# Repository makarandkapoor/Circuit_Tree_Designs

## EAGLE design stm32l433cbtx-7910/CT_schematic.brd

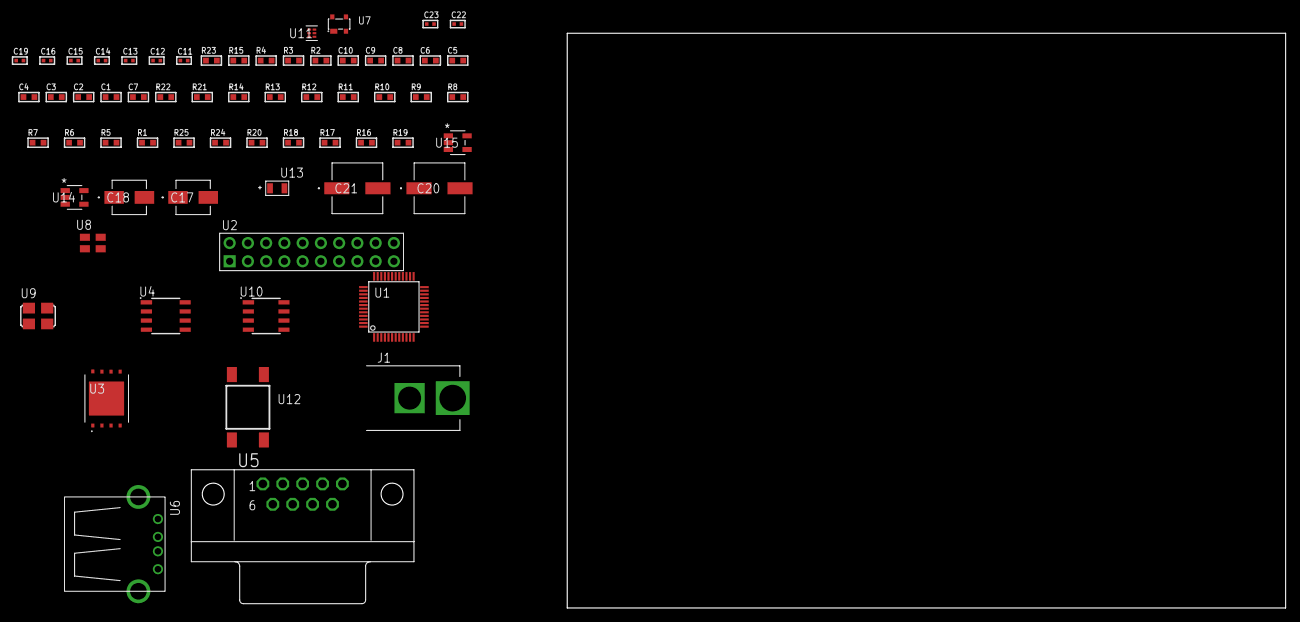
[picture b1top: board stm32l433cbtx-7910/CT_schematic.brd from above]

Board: 2 copper layers, 100.0 x 80.0 mm, 64 parts (0 on the bottom side), 37 nets, no tracks yet.

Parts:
C1, C9: 1e-06; C0603
C2, C3, C4, C5, C6, C10: 1e-07; C0603
C7: 4.7e-06; C0603
C8: 1e-08; C0603
C11, C12, C14, C19: 1e-07; C0402
C13, C15, C16, C22, C23: 1e-08; C0402
C17: 1e-06; EXV-9B
C18: 2.2e-06; EXV-9B
C20, C21: 0.0001; EXV-9H
J1: PJ-037B; PJ-037B_PACKAGE
R1, R5, R6, R7, R8, R9, R10, R11, R12, R13, R14, R21, R22: 10000.0; R0603
R2: 1000.0; R0603
R3: 1600.5; R0603
R4: 4700.0; R0603
R15: 120.0; R0603
R16: 470000.0; R0603
R17, R18, R20: 100000.0; R0603
R19: 164658.62; R0603
R23: 9100.0; R0603
R24: 680000.0; R0603
R25: 120000.0; R0603
U1: STM32L433CBT6; LQFP48
U2: TST-110-05-T-D-RA
U3: S25FL128SDPNFI001; WNG008
U4: SN65HVD230D; SOIC-8
U5: 182-009-113R531; 182-009-MALE
U6: 61400416021; USB-A-H
U7: prtr5v0u2ax; SOT143B
U8: ASEK-32.768KHz-ECST; ASEK
U9: ASFL1-25MHZ-NCS; ASFL1
U10: LP2954AIMX/NOPB; LP2954
U11: TPS3895ADRYR; SON-6
U12: 4-1437565-2; SW_4-1437565-2
U13: Q65110A2395; LGM67K-G1J2-24-Z
U14, U15: nc7sz125m5x; NC7SZ125M5X

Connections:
CLK_U1_3: U1.3, U8.3
CLK_U1_5: U1.5, U9.3
GND: C1.2, C2.2, C3.2, C4.2, C5.2, C6.2, C7.2, C8.2, C9.2, C10.2, C11.2, C12.2, C13.2, C14.2, C15.2, C16.2, C17.2, C18.2, C19.2, C20.2, C21.2, C22.2, C23.2, J1.2, R2.2, R5.2, R11.2, R16.2, R20.2, R23.2, R25.2, U1.8, U1.23, U1.35, U1.47, U2.4, U2.6, U2.8, U2.10, U2.12, U2.14, U2.16, U2.18, U2.20, U3.4, U3.PAD, U4.2, U5.5, U6.4, U6.5, U6.6, U7.1, U8.2, U9.2, U10.4, U11.2, U13.C, U14.2, U14.3, U15.1, U15.3
NET_U1_7: R4.1, U1.7, U15.4
NET_U1_43: R3.1, U1.43, U13.A
NET_U1_44: R1.1, R5.1, U1.44, U12.3, U12.4
NET_U2_19: R11.1, U2.19
NET_U3_3: R12.1, U3.3
NET_U3_7: R14.1, U3.7
NET_U4_6: R15.2, U4.6
NET_U4_8: R16.1, U4.8
NET_U5_2: R15.2, U4.6, U5.2
NET_U5_3: R15.1, U4.7, U5.3
NET_U7_4: U6.1, U7.4
NET_U10_3: R18.1, U10.3
NET_U10_5: R17.1, U10.5
NET_U10_7: R19.2, R20.1, U10.7
NET_U11_1: R22.1, R23.1, U11.1
NET_U11_3: R24.2, R25.1, U11.3
NET_U11_4: R21.1, U11.4, U14.4, U15.2
NET_U12_1: R2.1, U12.1, U12.2
PROC_CAN1_RX: U1.45, U4.4
PROC_CAN1_TX: U1.46, U4.1
PROC_SPI1_MISO: U1.16, U3.2
PROC_SPI1_MOSI: U1.17, U3.5
PROC_SPI1_NSS: R13.1, U1.14, U3.1
PROC_SPI1_SCK: U1.11, U3.6
PROC_SYS_JTCK_SWCLK: R9.1, U1.37, U2.9
PROC_SYS_JTDI: R7.1, U1.38, U2.5
PROC_SYS_JTDO_SWO: U1.39, U2.13
PROC_SYS_JTMS_SWDIO: R8.1, U1.34, U2.7
PROC_SYS_JTRST: R6.1, U1.40, U2.3
PROC_USB_DM: U1.32, U6.2, U7.3
PROC_USB_DP: U1.33, U6.3, U7.2
RST_OUT_U2_SRESET_B: R10.1, U2.15, U14.1
VCC_S1_9V7: C17.1, C20.1, C21.1, J1.1, R18.2, U10.8
VCC_TIER1_3V3: C1.1, C2.1, C3.1, C4.1, C5.1, C6.1, C7.1, C8.1, C9.1, C10.1, C11.1, C12.1, C13.1, C14.1, C15.1, C16.1, C18.1, C19.1, C22.1, C23.1, R1.2, R3.2, R4.2, R6.2, R7.2, R8.2, R9.2, R10.2, R12.2, R13.2, R14.2, R17.2, R19.1, R21.2, R22.2, R24.1, U1.1, U1.9, U1.24, U1.36, U1.48, U2.1, U2.2, U3.8, U4.3, U8.4, U9.4, U10.1, U11.6, U14.5, U15.5

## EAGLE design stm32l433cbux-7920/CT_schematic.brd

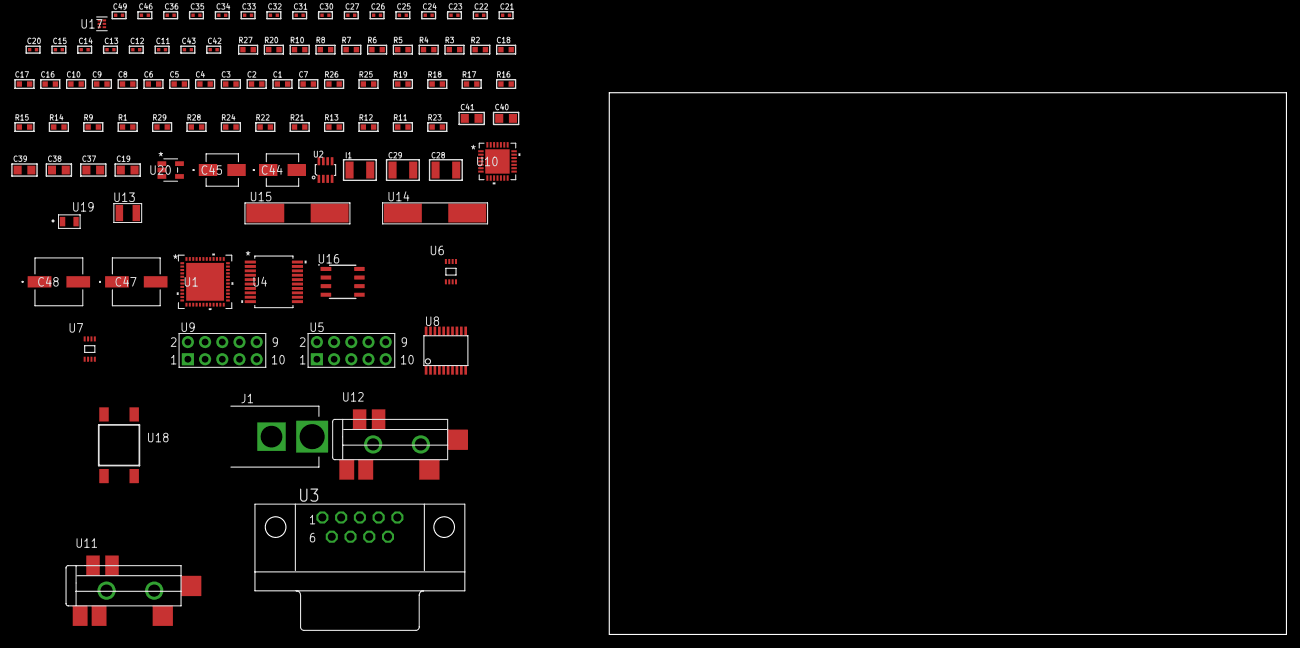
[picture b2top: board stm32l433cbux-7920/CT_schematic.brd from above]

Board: 2 copper layers, 100.0 x 80.0 mm, 100 parts (0 on the bottom side), 69 nets, no tracks yet.

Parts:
C1, C9, C16, C17, C18: 1e-06; C0603
C2, C3, C4, C5, C6, C10: 1e-07; C0603
C7: 4.7e-06; C0603
C8: 1e-08; C0603
C11, C12, C13, C14: 1e-11; C0402
C15, C22, C23, C24, C25, C26, C27, C32, C33, C34, C35, C36, C46: 1e-07; C0402
C19: 4.7e-06; C0805
C20, C21, C49: 1e-08; C0402
C28, C29: 2.2e-05; C1210
C30, C31: 1e-09; C0402
C37, C38, C39, C40, C41: 1e-05; C0805
C42, C43: 2.2e-11; C0402
C44: 1e-06; EXV-9B
C45: 2.2e-06; EXV-9B
C47, C48: 0.0001; EXV-9H
I1: 1.5e-05; L1210
J1: PJ-037B; PJ-037B_PACKAGE
R1, R9, R14, R15, R16, R25, R26: 10000.0; R0603
R2: 1000.0; R0603
R3: 1600.5; R0603
R4: 4700.0; R0603
R5, R6, R7, R8: 2200.0; R0603
R10: 120.0; R0603
R11, R12, R13, R21, R22, R24: 100000.0; R0603
R17, R18, R19: 47000.0; R0603
R20: 680.0; R0603
R23: 164658.62; R0603
R27: 9100.0; R0603
R28: 680000.0; R0603
R29: 120000.0; R0603
U1: STM32L433CBU6; UFQFPN48
U2: MAX3051EKA+T; SOT-23-8
U3: 182-009-113R531; 182-009-MALE
U4: MAX3218EAP+T; SSOP-20
U5, U9: HTSS-105-01-G-D
U6: 24AA00T-I/MNY; TDFN-8/6MM
U7: 24AA128T-I/MNY; TDFN-8/6MM
U8: SP3203ECY-L/TR; TSSOP20-I
U10: WM8731CLSEFL; QFN-28
U11, U12: SJ-43515TS-SMT-TR
U13: ABS07-32.768KHZ-7-T
U14: ABLS-25.000MHZ-B2F-T
U15: ABLS-12.288MHZ-B4-T
U16: LP2954AIMX/NOPB; LP2954
U17: TPS3895ADRYR; SON-6
U18: 4-1437565-2; SW_4-1437565-2
U19: Q65110A2395; LGM67K-G1J2-24-Z
U20: nc7sz125m5x; NC7SZ125M5X

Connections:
CLK_CRYSTAL_U1_3: C11.1, U1.3, U13.1
CLK_CRYSTAL_U1_4: C12.1, U1.4, U13.2
CLK_CRYSTAL_U1_5: C13.1, U1.5, U14.1
CLK_CRYSTAL_U1_6: C14.1, U1.6, U14.2
CLK_CRYSTAL_U10_1: C42.1, U10.1, U15.1
CLK_CRYSTAL_U10_2: C43.1, U10.2, U15.2
GND: C1.2, C2.2, C3.2, C4.2, C5.2, C6.2, C7.2, C8.2, C9.2, C10.2, C11.2, C12.2, C13.2, C14.2, C15.2, C16.2, C17.2, C18.2, C20.2, C21.2, C22.2, C23.2, C26.2, C27.2, C31.2, C32.2, C33.2, C34.2, C35.2, C36.2, C37.2, C38.2, C39.2, C40.2, C41.2, C42.2, C43.2, C44.2, C45.2, C46.2, C47.2, C48.2, C49.2, J1.2, R2.2, R9.2, R14.2, R16.2, R17.2, R18.2, R19.2, R24.2, R27.2, R29.2, U1.8, U1.23, U1.35, U1.47, U1.49, U2.2, U2.8, U3.5, U4.5, U4.17, U4.20, U5.9, U6.4, U7.4, U8.18, U9.9, U10.4, U10.15, U10.19, U10.25, U10.26, U10.29, U11.1, U12.1, U16.4, U17.2, U19.C, U20.1, U20.3
NET_U1_7: R4.1, U1.7, U20.4
NET_U1_21: R7.1, U1.21, U7.6
NET_U1_22: R8.1, U1.22, U7.5
NET_U1_31: R6.1, U1.31, U6.5
NET_U1_42: R5.1, U1.42, U6.6
NET_U1_44: R9.1, U1.44
NET_U1_45: R3.1, U1.45, U19.A
NET_U1_46: R1.1, U1.46, U18.3, U18.4
NET_U2_6: R10.2, U2.6
NET_U3_2: R10.2, U2.6, U3.2
NET_U3_3: R10.1, U2.7, U3.3
NET_U4_1: I1.1, U4.1
NET_U4_2: R11.1, U4.2
NET_U4_3: R12.1, U4.3
NET_U4_4: R13.1, U4.4
NET_U4_15: C18.1, U4.15
NET_U4_16: C19.2, U4.16
NET_U4_18: C19.1, U4.18
NET_U4_19: C17.1, U4.19
NET_U5_3: U4.12, U5.3
NET_U5_4: U4.11, U5.4
NET_U5_5: U4.14, U5.5
NET_U5_6: U4.13, U5.6
NET_U7_1: R14.1, U7.1
NET_U7_2: R15.1, U7.2
NET_U7_3: R16.1, U7.3
NET_U8_1: C24.1, U8.1
NET_U8_2: C26.1, U8.2
NET_U8_3: C24.2, U8.3
NET_U8_4: C25.1, U8.4
NET_U8_5: C25.2, U8.5
NET_U8_6: C27.1, U8.6
NET_U9_3: U8.14, U9.3
NET_U9_4: U8.13, U9.4
NET_U9_5: U8.17, U9.5
NET_U9_6: U8.16, U9.6
NET_U10_20: C36.1, C41.1, U10.20
NET_U11_2: C29.1, R18.1, U11.2
NET_U11_5: C28.1, R17.1, U11.5
NET_U12_5: C30.1, C31.1, R19.1, R20.1, U12.5
NET_U16_3: R22.1, U16.3
NET_U16_5: R21.1, U16.5
NET_U16_7: R23.2, R24.1, U16.7
NET_U17_1: R26.1, R27.1, U17.1
NET_U17_3: R28.2, R29.1, U17.3
NET_U17_4: R25.1, U17.4, U20.2
NET_U18_1: R2.1, U18.1, U18.2
PROC_CAN1_RX: U1.32, U2.4
PROC_CAN1_TX: U1.33, U2.1
PROC_LPUART1_CTS: U1.16, U4.8
PROC_LPUART1_RTS: U1.19, U4.10
PROC_LPUART1_RX: U1.13, U4.9
PROC_LPUART1_TX: U1.12, U4.7
PROC_SAI1_FS_A: U1.25, U10.9, U10.11
PROC_SAI1_SCK_A: U1.26, U10.7
PROC_SAI1_SD_A: U1.28, U10.8
PROC_USART1_CTS: U1.40, U8.8
PROC_USART1_RTS: U1.39, U8.10
PROC_USART1_RX: U1.43, U8.11
PROC_USART1_TX: U1.30, U8.7
VCC_S1_5V3: C44.1, C47.1, C48.1, J1.1, R22.2, U16.8
VCC_TIER1_3V3: C1.1, C2.1, C3.1, C4.1, C5.1, C6.1, C7.1, C8.1, C9.1, C10.1, C15.1, C16.1, C20.1, C21.1, C22.1, C23.1, C32.1, C33.1, C34.1, C35.1, C37.1, C38.1, C39.1, C40.1, C45.1, C46.1, C49.1, I1.2, R1.2, R3.2, R4.2, R5.2, R6.2, R7.2, R8.2, R11.2, R12.2, R13.2, R15.2, R21.2, R23.1, R25.2, R26.2, R28.1, U1.1, U1.9, U1.24, U1.36, U1.48, U2.3, U4.6, U6.8, U7.7, U7.8, U8.12, U8.19, U10.3, U10.5, U10.12, U10.18, U16.1, U17.6, U20.5

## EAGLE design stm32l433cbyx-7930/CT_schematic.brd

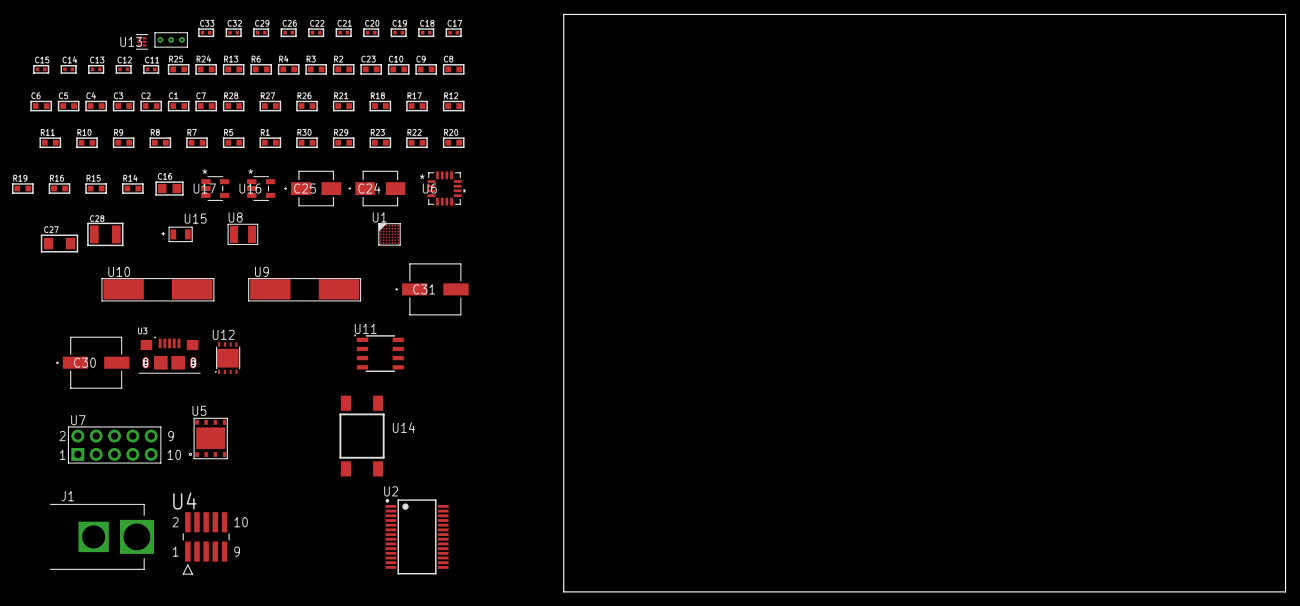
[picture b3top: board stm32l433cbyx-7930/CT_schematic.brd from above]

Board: 2 copper layers, 82 parts (0 on the bottom side), 57 nets, no tracks yet.

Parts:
C1, C9, C23: 1e-06; C0603
C2, C3, C4, C5, C6, C10: 1e-07; C0603
C7: 4.7e-06; C0603
C8: 1e-08; C0603
C11, C12, C13, C14: 1e-11; C0402
C15, C17, C18, C19, C20, C21, C22, C29: 1e-07; C0402
C16: 4.7e-06; C0805
C24: 1e-06; EXV-9B
C25: 2.2e-06; EXV-9B
C26, C32, C33: 1e-08; C0402
C27: 1e-05; C1206
C28: 1e-05; C1210
C30, C31: 0.0001; EXV-9H
J1: PJ-037B; PJ-037B_PACKAGE
R1, R5, R7, R8, R9, R10, R11, R12, R17, R18, R26, R27: 10000.0; R0603
R2, R25: 1000.0; R0603
R3: 910.0; R0603
R4, R6: 4700.0; R0603
R13: 5.0; R0603
R14, R15, R16, R19, R20, R22, R23: 100000.0; R0603
R21: 47000.0; R0603
R24: 2231.0; R0603
R28: 82000.0; R0603
R29: 300000.0; R0603
R30: 120000.0; R0603
U1: STM32L433CBY6; WLCSP49
U2: FT232RL-REEL; SSOP-28
U3: 10118193-0001LF; FCI_10118193-0001LF
U4: FTSH-105-01-L-DV-K; SAMTEC_FTSH-105-01-L-DV-K
U5: SST26WF016B-104I/MF; WFDN-8
U6: TSC2046IRGVR; VQFN-16
U7: HTSS-105-01-G-D
U8: ABS07-32.768KHZ-7-T
U9: ABLS-25.000MHZ-B2F-T
U10: ABLS-12.000MHZ-B4-T
U11: LP2954AIMX/NOPB; LP2954
U12: LP3878SDX-ADJ/NOPB; WSON-8
U13: TPS3895ADRYR; SON-6
U14: 4-1437565-2; SW_4-1437565-2
U15: Q65110A2395; LGM67K-G1J2-24-Z
U16, U17: nc7sz125m5x; NC7SZ125M5X
U18: Dummy; DUMMY_PACKAGE_172

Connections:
CLK_CRYSTAL_U1_C6: C11.1, U1.C6, U8.1
CLK_CRYSTAL_U1_C7: C12.1, U1.C7, U8.2
CLK_CRYSTAL_U1_D6: C13.1, U1.D6, U9.1
CLK_CRYSTAL_U1_D7: C14.1, U1.D7, U9.2
CLK_CRYSTAL_U2_27: U2.27, U10.1
CLK_CRYSTAL_U2_28: U2.28, U10.2
GND: C1.2, C2.2, C3.2, C4.2, C5.2, C6.2, C7.2, C8.2, C9.2, C10.2, C11.2, C12.2, C13.2, C14.2, C15.2, C16.2, C17.2, C18.2, C19.2, C20.2, C21.2, C22.2, C23.2, C24.2, C25.2, C26.2, C27.2, C28.2, C29.2, C30.2, C31.2, C32.2, C33.2, J1.2, R2.2, R5.2, R8.2, R12.2, R13.2, R22.2, R25.2, R28.2, R30.2, U1.A6, U1.B1, U1.E7, U1.G2, U2.7, U2.18, U2.21, U2.25, U2.26, U3.5, U3.6, U3.7, U3.8, U3.9, U4.3, U4.5, U5.4, U5.9, U6.10, U7.9, U11.4, U12.3, U12.PAD, U13.2, U15.C, U16.2, U16.3, U17.1, U17.3, U18.1
NET_U1_A5: R5.1, U1.A5
NET_U1_D5: R4.1, U1.D5, U17.4
NET_U1_G3: R3.1, U1.G3, U15.A
NET_U1_G7: R1.1, U1.G7, U14.3, U14.4
NET_U2_14: R7.1, U2.14
NET_U2_17: C17.1, U2.17
NET_U2_19: R8.1, U2.19
NET_U3_1: R6.1, U3.1
NET_U3_2: U2.16, U3.2
NET_U3_3: U2.15, U3.3
NET_U4_9: R13.1, U4.9
NET_U6_15: R18.1, U6.15
NET_U7_3: U6.7, U7.3
NET_U7_4: U6.9, U7.4
NET_U7_5: U6.6, U7.5
NET_U7_6: U6.8, U7.6
NET_U11_3: R20.1, U11.3
NET_U11_5: R19.1, U11.5
NET_U11_7: R21.2, R22.1, U11.7
NET_U12_1: C26.1, U12.1
NET_U12_6: R24.2, R25.1, U12.6
NET_U12_8: R23.1, U12.8
NET_U13_1: R27.1, R28.1, U13.1
NET_U13_3: R29.2, R30.1, U13.3
NET_U13_4: R26.1, U13.4, U16.4, U17.2
NET_U14_1: R2.1, U14.1, U14.2
PROC_LPUART1_CTS: U1.E2, U2.3
PROC_LPUART1_RTS: U1.F1, U2.11
PROC_LPUART1_RX: U1.E4, U2.1
PROC_LPUART1_TX: U1.F2, U2.5
PROC_QUADSPI_BK1_IO0: U1.G4, U5.5
PROC_QUADSPI_BK1_IO1: U1.G5, U5.2
PROC_QUADSPI_BK1_IO2: R15.1, U1.F3, U5.3
PROC_QUADSPI_BK1_IO3: R16.1, U1.F4, U5.7
PROC_QUADSPI_BK1_NCS: R14.1, U1.E5, U5.1
PROC_QUADSPI_CLK: U1.E3, U5.6
PROC_SPI1_MISO: U1.A4, U6.16
PROC_SPI1_MOSI: U1.B4, U6.2
PROC_SPI1_NSS: R17.1, U1.G6, U6.3
PROC_SPI1_SCK: U1.F5, U6.4
PROC_SYS_JTCK_SWCLK: R12.1, U1.A2, U4.4
PROC_SYS_JTDI: R10.1, U1.B3, U4.8
PROC_SYS_JTDO_SWO: U1.A3, U4.6
PROC_SYS_JTMS_SWDIO: R11.1, U1.B2, U4.2
PROC_TIM1_CH2: U1.D2, U18.2
PROC_TIM1_CH4: U1.C1, U18.3
RST_OUT_U4_JTAG_RST_B: R9.1, U4.10, U16.1
VCC_S1_8V5: C24.1, C27.1, C30.1, C31.1, J1.1, R20.2, R23.2, U11.8, U12.4
VCC_TIER1_1V8: C1.1, C2.1, C3.1, C4.1, C5.1, C6.1, C7.1, C8.1, C9.1, C10.1, C18.1, C19.1, C20.1, C21.1, C25.1, C29.1, C32.1, C33.1, R1.2, R3.2, R4.2, R9.2, R10.2, R11.2, R14.2, R15.2, R16.2, R17.2, R18.2, R19.2, R21.1, R26.2, R27.2, R29.1, U1.A1, U1.A7, U1.B6, U1.F7, U1.G1, U2.4, U4.1, U5.8, U6.14, U11.1, U13.6, U16.5, U17.5
VCC_TIER1_3V3: C15.1, C16.1, C22.1, C23.1, C28.1, R7.2, R24.1, U2.20, U6.5, U12.5

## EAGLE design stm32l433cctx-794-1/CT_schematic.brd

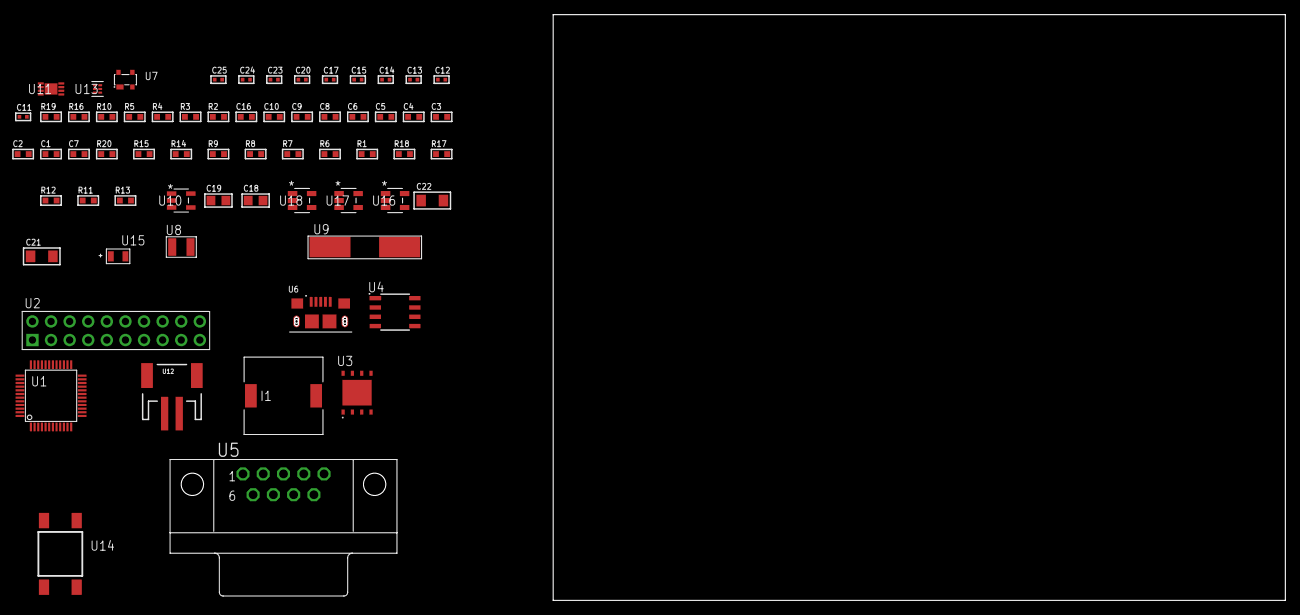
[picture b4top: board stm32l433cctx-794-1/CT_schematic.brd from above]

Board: 2 copper layers, 64 parts (0 on the bottom side), 38 nets, no tracks yet.

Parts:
C1, C9, C16: 1e-06; C0603
C2, C3, C4, C5, C6, C10: 1e-07; C0603
C7: 4.7e-06; C0603
C8: 1e-08; C0603
C11, C12, C13, C14: 1e-11; C0402
C15, C17, C20: 1e-07; C0402
C18, C19: 1e-05; C0805
C21, C22: 1e-05; C1206
C23, C24, C25: 1e-08; C0402
I1: 5.2e-06; DR1040
R1, R6, R7, R8, R9, R14, R15, R20: 10000.0; R0603
R2: 1000.0; R0603
R3: 1600.5; R0603
R4, R5: 4700.0; R0603
R10: 120.0; R0603
R11: 100000.0; R0603
R12: 220000.0; R0603
R13: 1000000.0; R0603
R16: 9100.0; R0603
R17: 680000.0; R0603
R18: 120000.0; R0603
R19: 2000.0; R0603
U1: STM32L433CCT6; LQFP48
U2: TST-110-05-T-D-RA
U3: MX25R6435FZAIH0; WSON-8-PAD
U4: SN65HVD230D; SOIC-8
U5: 182-009-113R531; 182-009-MALE
U6: 10118193-0001LF; FCI_10118193-0001LF
U7: prtr5v0u2ax; SOT143B
U8: ABS07-32.768KHZ-7-T
U9: ABLS-25.000MHZ-B2F-T
U10: ltc3406es5; TSOT-23-5
U11: MCP73831T-2ACI/MC; DFN8_2X3MC
U12: S2B-PH-SM4-TB(LF)(SN); JST-2-SMD
U13: TPS3895ADRYR; SON-6
U14: 4-1437565-2; SW_4-1437565-2
U15: Q65110A2395; LGM67K-G1J2-24-Z
U16, U17, U18: nc7sz125m5x; NC7SZ125M5X

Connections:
CLK_CRYSTAL_U1_3: C11.1, U1.3, U8.1
CLK_CRYSTAL_U1_4: C12.1, U1.4, U8.2
CLK_CRYSTAL_U1_5: C13.1, U1.5, U9.1
CLK_CRYSTAL_U1_6: C14.1, U1.6, U9.2
GND: C1.2, C2.2, C3.2, C4.2, C5.2, C6.2, C7.2, C8.2, C9.2, C10.2, C11.2, C12.2, C13.2, C14.2, C15.2, C16.2, C17.2, C18.2, C19.1, C19.2, C20.2, C21.2, C22.2, C23.2, C24.2, C25.2, R2.2, R6.2, R11.2, R12.2, R16.2, R18.2, R19.2, U1.8, U1.23, U1.35, U1.47, U2.4, U2.6, U2.8, U2.10, U2.12, U2.14, U2.16, U2.18, U2.20, U3.4, U3.PAD, U4.2, U5.5, U6.5, U6.6, U6.7, U6.8, U6.9, U7.1, U10.2, U11.6, U11.9, U12.2, U13.2, U15.C, U16.2, U16.3, U17.1, U17.3, U18.1, U18.3
INPUT_USBPOWER_5V: C21.1, R20.2, U6.1, U7.4, U11.1, U11.2
NET_U1_7: R5.1, U1.7, U18.4
NET_U1_43: R3.1, U1.43, U15.A
NET_U1_44: R1.1, R6.1, U1.44, U14.3, U14.4
NET_U3_7: R4.1, U1.16, U3.7, U17.4
NET_U4_6: R10.2, U4.6
NET_U4_8: R11.1, U4.8
NET_U5_2: R10.2, U4.6, U5.2
NET_U5_3: R10.1, U4.7, U5.3
NET_U10_3: I1.1, U10.3
NET_U10_5: R12.1, R13.1, U10.5
NET_U10_ATNET_3: I1.2, R13.2
NET_U11_5: R20.1, U11.5
NET_U11_8: R19.1, U11.8
NET_U13_1: R15.1, R16.1, U13.1
NET_U13_3: R17.2, R18.1, U13.3
NET_U13_4: R14.1, U13.4, U16.4, U17.2, U18.2
NET_U14_1: R2.1, U14.1, U14.2
PROC_CAN1_RX: U1.45, U4.4
PROC_CAN1_TX: U1.46, U4.1
PROC_QUADSPI_BK1_IO0: U1.19, U3.5
PROC_QUADSPI_BK1_IO1: U1.18, U3.2
PROC_QUADSPI_BK1_IO2: R9.1, U1.17, U3.3
PROC_QUADSPI_BK1_NCS: R8.1, U1.12, U3.1
PROC_QUADSPI_CLK: U1.13, U3.6
PROC_SYS_JTCK_SWCLK: U1.37, U2.9
PROC_SYS_JTDO_SWO: U1.39, U2.13
PROC_SYS_JTMS_SWDIO: U1.34, U2.7
PROC_USB_DM: U1.32, U6.2, U7.3
PROC_USB_DP: U1.33, U6.3, U7.2
RST_OUT_U2_SRESET_B: R7.1, U2.15, U16.1
VCC_S1_3V7: C18.1, C22.1, U10.4, U11.3, U11.4, U12.1
VCC_TIER1_3V3: C1.1, C2.1, C3.1, C4.1, C5.1, C6.1, C7.1, C8.1, C9.1, C10.1, C15.1, C16.1, C17.1, C19.2, C20.1, C23.1, C24.1, C25.1, I1.2, R1.2, R3.2, R4.2, R5.2, R7.2, R8.2, R9.2, R13.2, R14.2, R15.2, R17.1, U1.1, U1.9, U1.24, U1.36, U1.48, U2.1, U3.8, U4.3, U13.6, U16.5, U17.5, U18.5

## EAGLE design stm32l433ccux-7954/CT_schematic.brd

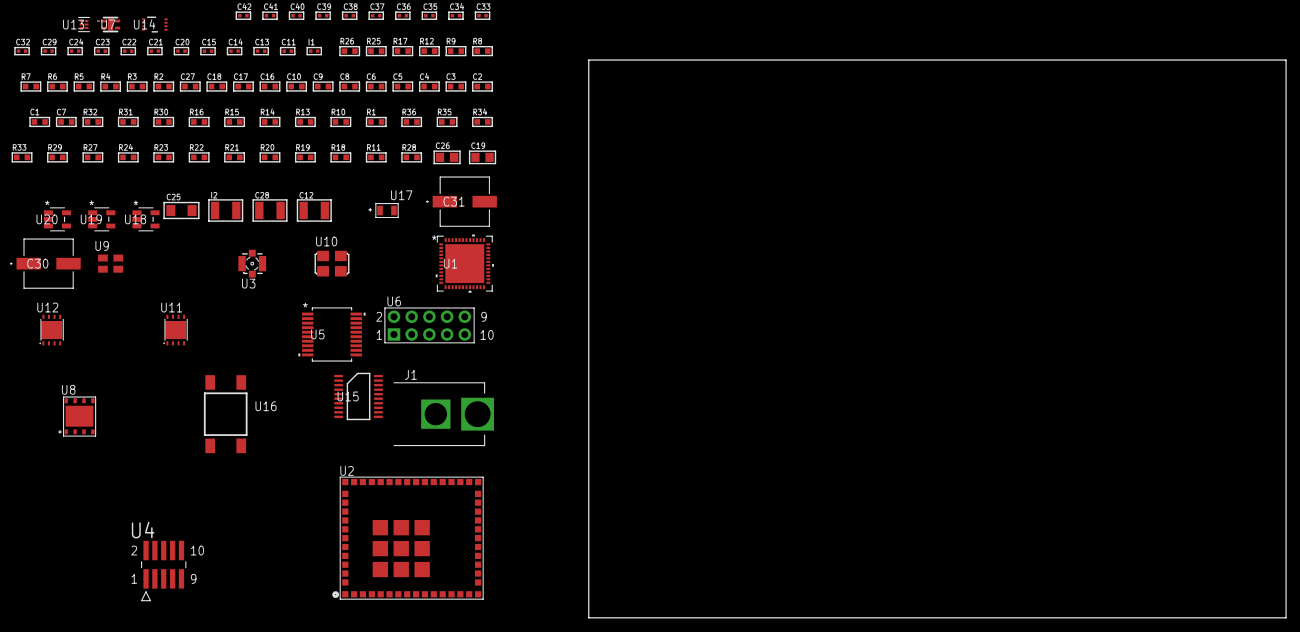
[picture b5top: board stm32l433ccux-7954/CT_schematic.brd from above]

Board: 2 copper layers, 100.0 x 80.0 mm, 101 parts (0 on the bottom side), 65 nets, no tracks yet.

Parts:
C1, C9, C16, C17, C18, C27: 1e-06; C0603
C2, C3, C4, C5, C6, C10: 1e-07; C0603
C7: 4.7e-06; C0603
C8: 1e-08; C0603
C11: 1e-12; C0402
C12: 2.2e-05; C1210
C13, C14, C15, C20, C21, C29, C33, C35, C37, C39: 1e-07; C0402
C19: 4.7e-06; C0805
C22, C23, C24, C32, C34, C36, C38, C40, C41, C42: 1e-08; C0402
C25: 1e-05; C1206
C26: 1e-05; C0805
C28: 1e-05; C1210
C30, C31: 0.0001; EXV-9H
I1: 3.6e-09; C0402
I2: 1.5e-05; L1210
J1: PJ-037B; PJ-037B_PACKAGE
R1, R10, R13, R14, R15, R16, R30, R31: 10000.0; R0603
R2, R26: 1000.0; R0603
R3: 910.0; R0603
R4, R5: 4700.0; R0603
R6, R7, R8, R9: 2200.0; R0603
R11, R18, R19, R20, R21, R22, R23, R24, R27, R29: 100000.0; R0603
R12: 2700.0; R0603
R17: 5.0; R0603
R25: 806.0; R0603
R28: 153694.38; R0603
R32: 82000.0; R0603
R33: 300000.0; R0603
R34: 120000.0; R0603
R35, R36: 200000.0; R0603
U1: STM32L433CCU6; UFQFPN48
U2: CC3200MODR1M2AMOBT; LGA63S127P16X13_2050X1750X150
U3: 73412-0114; COAXIAL_C
U4: FTSH-105-01-L-DV-K; SAMTEC_FTSH-105-01-L-DV-K
U5: MAX3218EAP+T; SSOP-20
U6: HTSS-105-01-G-D
U7: Si7034-A10-IM; SI7034-A10-IM
U8: SST26VF032B-104I/MF; WFDN-8
U9: ASEK-32.768KHz-ECST; ASEK
U10: ASFL1-25MHZ-NCS; ASFL1
U11: LP3878SDX-ADJ/NOPB; WSON-8
U12: LP2951ACSDX/NOPB; WSON-8
U13: TPS3895ADRYR; SON-6
U14: LSF0102DCTR; DCU0008A_N
U15: LSF0108PWR; PW0020A
U16: 4-1437565-2; SW_4-1437565-2
U17: Q65110A2395; LGM67K-G1J2-24-Z
U18, U19, U20: nc7sz125m5x; NC7SZ125M5X

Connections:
CLK_U1_3: U1.3, U9.3
CLK_U1_5: U1.5, U10.3
GND: C1.2, C2.2, C3.2, C4.2, C5.2, C6.2, C7.2, C8.2, C9.2, C10.2, C11.2, C12.2, C13.2, C14.2, C15.2, C16.2, C17.2, C18.2, C20.2, C21.2, C22.2, C23.2, C24.2, C25.2, C26.2, C27.2, C28.2, C29.2, C30.2, C31.2, C32.2, C33.2, C34.2, C35.2, C36.2, C37.2, C38.2, C39.2, C40.2, C41.2, C42.2, J1.2, R2.2, R10.2, R11.2, R12.2, R16.2, R17.2, R26.2, R29.2, R32.2, R34.2, U1.8, U1.23, U1.35, U1.47, U1.49, U2.1, U2.2, U2.16, U2.27, U2.28, U2.30, U2.32, U2.38, U2.43, U2.55, U2.56, U2.57, U2.58, U2.59, U2.60, U2.61, U2.62, U2.63, U3.1, U3.2, U3.3, U3.4, U4.3, U4.5, U5.5, U5.17, U5.20, U6.9, U7.5, U8.4, U8.9, U9.2, U10.2, U11.3, U11.PAD, U12.3, U12.4, U12.PAD, U13.2, U14.1, U15.1, U17.C, U18.2, U18.3, U19.1, U19.3, U20.1, U20.3
NET_U1_7: R5.1, U1.7, U20.4
NET_U1_21: R8.1, U1.21, U7.2
NET_U1_22: R9.1, U1.22, U7.4
NET_U1_31: R7.1, U1.31, U14.3
NET_U1_42: R6.1, U1.42, U14.4
NET_U1_44: R10.1, U1.44
NET_U1_45: R3.1, U1.45, U17.A
NET_U1_46: R1.1, U1.46, U16.3, U16.4
NET_U2_21: R11.1, U2.21
NET_U2_23: R12.1, U2.23
NET_U2_35: R4.1, U2.35, U19.4
NET_U3_1: C11.1, I1.1, U3.1
NET_U4_9: R17.1, U4.9
NET_U5_1: I2.1, U5.1
NET_U5_2: R18.1, U5.2
NET_U5_3: R19.1, U5.3
NET_U5_4: R20.1, U5.4
NET_U5_15: C18.1, U5.15
NET_U5_16: C19.2, U5.16
NET_U5_18: C19.1, U5.18
NET_U5_19: C17.1, U5.19
NET_U6_3: U5.12, U6.3
NET_U6_4: U5.11, U6.4
NET_U6_5: U5.14, U6.5
NET_U6_6: U5.13, U6.6
NET_U11_1: C24.1, U11.1
NET_U11_6: R25.2, R26.1, U11.6
NET_U11_8: R24.1, U11.8
NET_U12_5: R27.1, U12.5
NET_U12_7: R28.2, R29.1, U12.7
NET_U13_1: R31.1, R32.1, U13.1
NET_U13_3: R33.2, R34.1, U13.3
NET_U13_4: R30.1, U13.4, U18.4, U19.2, U20.2
NET_U14_8: R35.1, U14.8
NET_U15_20: R36.1, U15.20
NET_U16_1: R2.1, U16.1, U16.2
PROC_I2C1_SCL_TOXCVR: U2.3, U14.5
PROC_I2C1_SDA_TOXCVR: U2.4, U14.6
PROC_QUADSPI_BK1_IO0_TOIOBUF: U1.19, U15.3
PROC_QUADSPI_BK1_IO0_TOXCVR: U8.5, U15.18
PROC_QUADSPI_BK1_IO1_TOIOBUF: U1.18, U15.7
PROC_QUADSPI_BK1_IO1_TOXCVR: U8.2, U15.14
PROC_QUADSPI_BK1_IO2_TOIOBUF: U1.17, U15.5
PROC_QUADSPI_BK1_IO2_TOXCVR: R22.1, U8.3, U15.16
PROC_QUADSPI_BK1_IO3_TOIOBUF: U1.16, U15.8
PROC_QUADSPI_BK1_IO3_TOXCVR: R23.1, U8.7, U15.13
PROC_QUADSPI_BK1_NCS_TOIOBUF: U1.12, U15.6
PROC_QUADSPI_BK1_NCS_TOXCVR: R21.1, U8.1, U15.15
PROC_QUADSPI_CLK_TOIOBUF: U1.13, U15.4
PROC_QUADSPI_CLK_TOXCVR: U8.6, U15.17
PROC_SYS_JTCK_SWCLK: R16.1, U1.37, U4.4
PROC_SYS_JTDI: R14.1, U1.38, U4.8
PROC_SYS_JTDO_SWO: U1.39, U4.6
PROC_SYS_JTMS_SWDIO: R15.1, U1.34, U4.2
PROC_USART1_CTS: U1.32, U5.8
PROC_USART1_RTS: U1.33, U5.10
PROC_USART1_RX: U1.43, U5.9
PROC_USART1_TX: U1.30, U5.7
RST_OUT_U4_JTAG_RST_B: R13.1, U4.10, U18.1
VCC_S1_7V4: C25.1, C27.1, C30.1, C31.1, J1.1, R24.2, U11.4, U12.8
VCC_TIER1_1V8: C1.1, C2.1, C3.1, C4.1, C5.1, C6.1, C7.1, C10.1, C15.1, C16.1, C20.1, C26.1, C29.1, C34.1, C35.1, C38.1, C39.1, C40.1, C41.1, C42.1, I2.2, R1.2, R3.2, R5.2, R6.2, R7.2, R8.2, R9.2, R13.2, R14.2, R15.2, R18.2, R19.2, R20.2, R25.1, R30.2, R31.2, R33.1, U1.1, U1.24, U1.36, U1.48, U4.1, U5.6, U7.1, U11.5, U13.6, U14.2, U15.2, U18.5, U19.5, U20.5
VCC_TIER1_3V3: C8.1, C9.1, C12.1, C13.1, C14.1, C21.1, C22.1, C23.1, C28.1, C32.1, C33.1, C36.1, C37.1, R4.2, R21.2, R22.2, R23.2, R27.2, R28.1, R35.2, R36.2, U1.9, U2.36, U2.37, U2.40, U8.8, U9.4, U10.4, U12.1, U14.7, U15.19

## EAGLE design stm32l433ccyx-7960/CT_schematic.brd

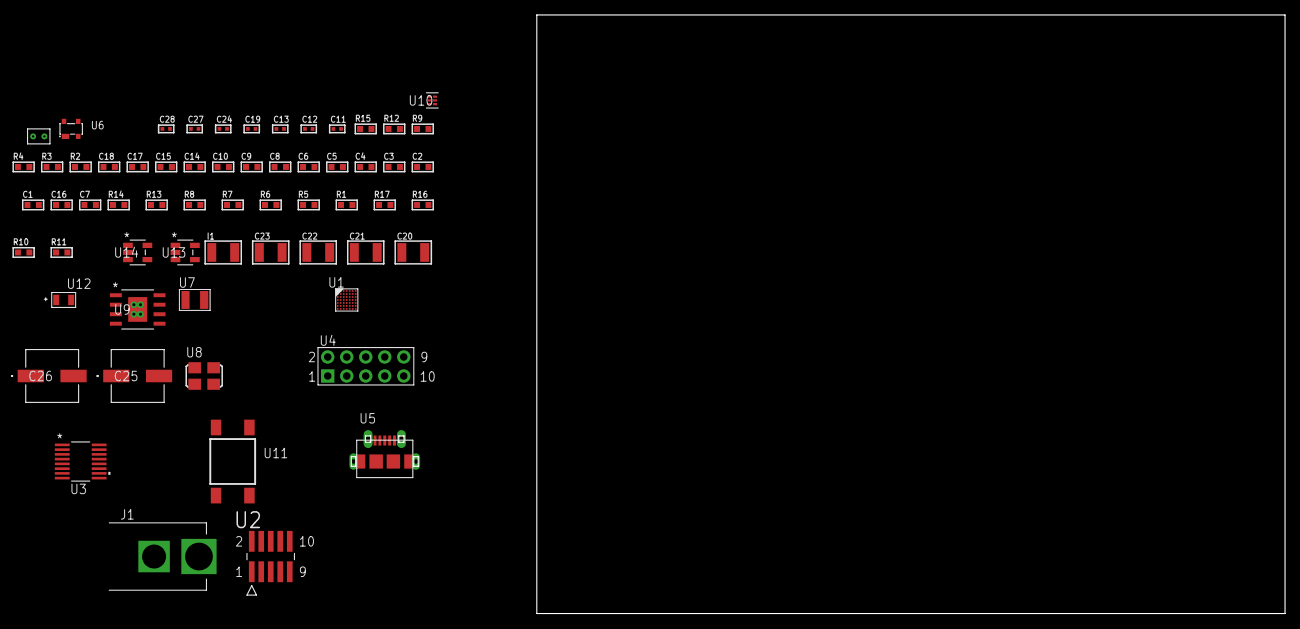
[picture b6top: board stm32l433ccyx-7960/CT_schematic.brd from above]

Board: 2 copper layers, 124.8 x 80.0 mm, 62 parts (0 on the bottom side), 37 nets, no tracks yet.

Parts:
C1, C9, C14, C15, C17, C18: 1e-06; C0603
C2, C3, C4, C5, C6, C10: 1e-07; C0603
C7: 4.7e-06; C0603
C8: 1e-08; C0603
C11, C12: 1e-11; C0402
C13, C24: 1e-07; C0402
C16: 2.2e-07; C0603
C19, C27, C28: 1e-08; C0402
C20, C21, C22, C23: 1e-05; C1210
C25, C26: 0.0001; EXV-9H
I1: 1e-05; L1210
J1: PJ-037B; PJ-037B_PACKAGE
R1, R5, R6, R7, R8, R13, R14: 10000.0; R0603
R2: 1000.0; R0603
R3: 1600.5; R0603
R4: 4700.0; R0603
R9: 5.0; R0603
R10: 100000.0; R0603
R11: 4031.5447154472; R0603
R12: 2200.0; R0603
R15: 9100.0; R0603
R16: 680000.0; R0603
R17: 120000.0; R0603
U1: STM32L433CCY6; WLCSP49
U2: FTSH-105-01-L-DV-K; SAMTEC_FTSH-105-01-L-DV-K
U3: LTC2804CGN-1#PBF; SSOP-16
U4: HTSS-105-01-G-D
U5: 47590-0001; MICRO_USB_AB
U6: prtr5v0u2ax; SOT143B
U7: ABS07-32.768KHZ-7-T
U8: ASFL1-25MHZ-NCS; ASFL1
U9: MIC5234YME; SOIC-8_EP
U10: TPS3895ADRYR; SON-6
U11: 4-1437565-2; SW_4-1437565-2
U12: Q65110A2395; LGM67K-G1J2-24-Z
U13, U14: nc7sz125m5x; NC7SZ125M5X
U15: Dummy; DUMMY_PACKAGE_127

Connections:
CLK_CRYSTAL_U1_C6: C11.1, U1.C6, U7.1
CLK_CRYSTAL_U1_C7: C12.1, U1.C7, U7.2
CLK_U1_D7: U1.D7, U8.3
GND: C1.2, C2.2, C3.2, C4.2, C5.2, C6.2, C7.2, C8.2, C9.2, C10.2, C11.2, C12.2, C13.2, C14.2, C15.2, C17.2, C18.2, C19.2, C20.2, C21.2, C22.2, C23.2, C24.2, C25.2, C26.2, C27.2, C28.2, J1.2, R2.2, R5.2, R9.2, R12.2, R15.2, R17.2, U1.A6, U1.B1, U1.E7, U1.G2, U2.3, U2.5, U3.8, U4.9, U5.5, U5.6, U5.7, U5.8, U5.9, U6.1, U8.2, U9.7, U9.EPAD, U10.2, U12.C, U13.2, U13.3, U14.1, U14.3, U15.1
NET_U1_A5: R5.1, U1.A5
NET_U1_D5: R4.1, U1.D5, U14.4
NET_U1_G6: R3.1, U1.G6, U12.A
NET_U1_G7: R1.1, U1.G7, U11.3, U11.4
NET_U2_9: R9.1, U2.9
NET_U3_6: C14.1, U3.6
NET_U3_7: C16.1, I1.2, U3.7
NET_U3_9: C15.1, U3.9
NET_U3_10: C16.2, U3.10
NET_U3_11: R10.1, U3.11
NET_U4_3: U3.1, U4.3
NET_U4_4: U3.2, U4.4
NET_U4_5: U3.3, U4.5
NET_U4_6: U3.4, U4.6
NET_U6_4: U5.1, U6.4
NET_U9_4: R11.2, R12.1, U9.4
NET_U10_1: R14.1, R15.1, U10.1
NET_U10_3: R16.2, R17.1, U10.3
NET_U10_4: R13.1, U10.4, U13.4, U14.2
NET_U11_1: R2.1, U11.1, U11.2
PROC_DAC1_OUT2: U1.F5, U15.2
PROC_LPUART1_CTS: U1.E2, U3.13
PROC_LPUART1_RTS: U1.F1, U3.15
PROC_LPUART1_RX: U1.E3, U3.16
PROC_LPUART1_TX: U1.E5, U3.14
PROC_SYS_JTCK_SWCLK: R7.1, U1.A2, U2.4
PROC_SYS_JTDO_SWO: U1.A3, U2.6
PROC_SYS_JTMS_SWDIO: R8.1, U1.B2, U2.2
PROC_USB_DM: U1.C1, U5.2, U6.3
PROC_USB_DP: U1.C3, U5.3, U6.2
RST_OUT_U2_JTAG_RST_B: R6.1, U2.10, U13.1
VCC_S1_10V8: C20.1, C21.1, C25.1, C26.1, J1.1, U9.5, U9.8
VCC_TIER1_3V3: C1.1, C2.1, C3.1, C4.1, C5.1, C6.1, C7.1, C8.1, C9.1, C10.1, C13.1, C17.1, C18.1, C19.1, C22.1, C23.1, C24.1, C27.1, C28.1, I1.1, R1.2, R3.2, R4.2, R6.2, R7.2, R8.2, R10.2, R11.1, R13.2, R14.2, R16.1, U1.A1, U1.A7, U1.B6, U1.F7, U1.G1, U2.1, U3.5, U3.12, U8.4, U9.1, U10.6, U13.5, U14.5

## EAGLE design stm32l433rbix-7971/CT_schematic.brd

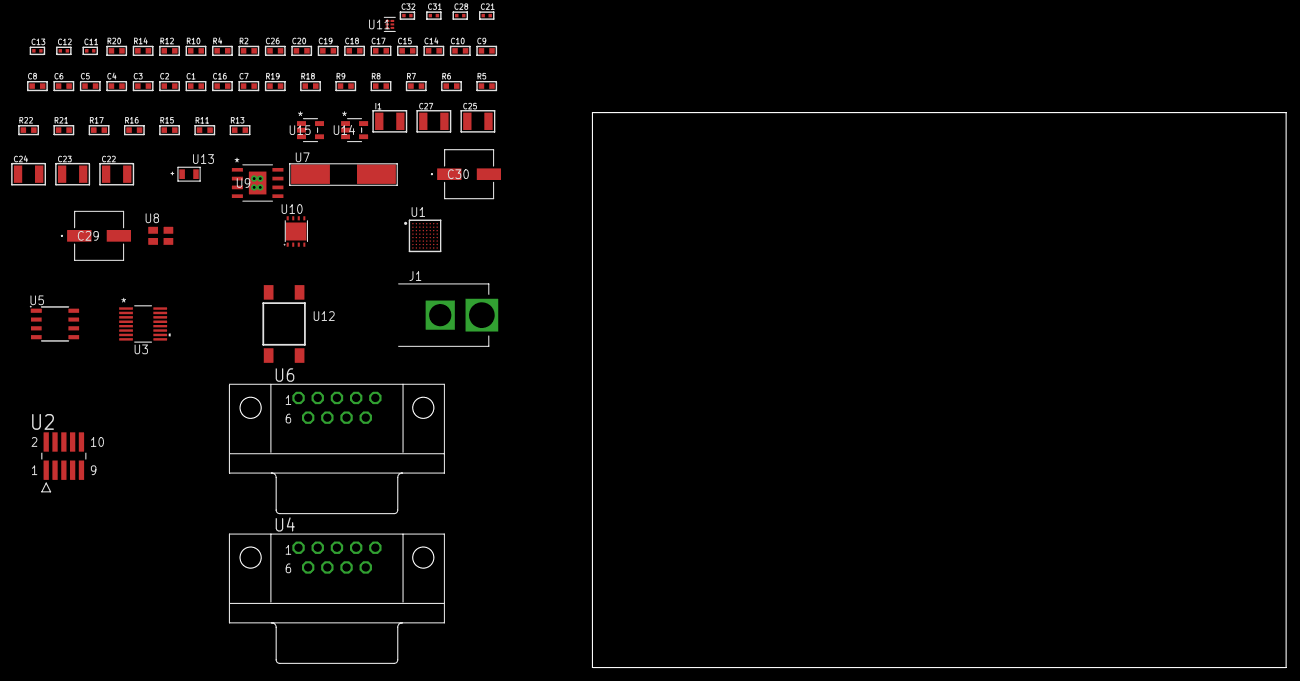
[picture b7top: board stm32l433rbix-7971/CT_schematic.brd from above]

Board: 2 copper layers, 100.0 x 80.0 mm, 69 parts (0 on the bottom side), 41 nets, no tracks yet.

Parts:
C1, C9, C14, C15, C17, C18, C19, C20: 1e-06; C0603
C2, C3, C4, C5, C6, C10: 1e-07; C0603
C7: 4.7e-06; C0603
C8: 1e-08; C0603
C11, C12: 1e-11; C0402
C13, C28: 1e-07; C0402
C16: 2.2e-07; C0603
C21, C31, C32: 1e-08; C0402
C22, C23, C24, C25, C27: 1e-05; C1210
C26: 8e-07; R0603
C29, C30: 0.0001; EXV-9H
I1: 1e-05; L1210
J1: PJ-037B; PJ-037B_PACKAGE
R2: 1000.0; R0603
R4: 4700.0; R0603
R5, R6, R7, R8, R9, R18, R19: 10000.0; R0603
R10: 5.0; R0603
R11, R15, R17: 100000.0; R0603
R12: 120.0; R0603
R13: 4031.5447154472; R0603
R14: 2200.0; R0603
R16: 300000.0; R0603
R20: 9100.0; R0603
R21: 680000.0; R0603
R22: 120000.0; R0603
U1: STM32L433RBI6; UFBGA64
U2: FTSH-105-01-L-DV-K; SAMTEC_FTSH-105-01-L-DV-K
U3: LTC2804CGN-1#PBF; SSOP-16
U4, U6: 182-009-113R531; 182-009-MALE
U5: MCP2562-E/SN; SOIC-8
U7: ABLS-25.000MHZ-B2F-T
U8: ASEK-32.768KHz-ECST; ASEK
U9: MIC5234YME; SOIC-8_EP
U10: LP2951ACSDX/NOPB; WSON-8
U11: TPS3895ADRYR; SON-6
U12: 4-1437565-2; SW_4-1437565-2
U13: Q65110A2395; LGM67K-G1J2-24-Z
U14, U15: nc7sz125m5x; NC7SZ125M5X

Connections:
CLK_CRYSTAL_U1_C1: C11.1, U1.C1, U7.1
CLK_CRYSTAL_U1_D1: C12.1, U1.D1, U7.2
CLK_U1_A1: U1.A1, U8.3
GND: C1.2, C2.2, C3.2, C4.2, C5.2, C6.2, C7.2, C8.2, C9.2, C10.2, C11.2, C12.2, C13.2, C14.2, C15.2, C17.2, C18.2, C19.2, C20.2, C21.2, C22.2, C23.2, C24.2, C25.2, C26.2, C27.2, C28.2, C29.2, C30.2, C31.2, C32.2, J1.2, R2.2, R5.2, R9.2, R10.2, R14.2, R17.2, R20.2, R22.2, U1.C2, U1.D4, U1.D5, U1.D6, U1.F1, U2.3, U2.5, U3.8, U4.5, U5.2, U5.8, U6.5, U8.2, U9.7, U9.EPAD, U10.3, U10.4, U10.PAD, U11.2, U13.C, U14.2, U14.3, U15.1, U15.3
NET_U1_B4: R5.1, U1.B4
NET_U1_E1: R4.1, U1.E1, U15.4
NET_U1_H8: U12.3, U12.4
NET_U2_9: R10.1, U2.9
NET_U3_6: C14.1, U3.6
NET_U3_7: C16.1, I1.2, U3.7
NET_U3_9: C15.1, U3.9
NET_U3_10: C16.2, U3.10
NET_U3_11: R11.1, U3.11
NET_U4_2: U3.1, U4.2
NET_U4_3: U3.3, U4.3
NET_U4_7: U3.2, U4.7
NET_U4_8: U3.4, U4.8
NET_U5_6: R12.2, U5.6
NET_U6_2: R12.2, U5.6, U6.2
NET_U6_3: R12.1, U5.7, U6.3
NET_U9_4: R13.2, R14.1, U9.4
NET_U10_5: R15.1, U10.5
NET_U10_7: R16.2, R17.1, U10.7
NET_U11_1: R19.1, R20.1, U11.1
NET_U11_3: R21.2, R22.1, U11.3
NET_U11_4: R18.1, U11.4, U14.4, U15.2
NET_U12_1: R2.1, U12.1, U12.2
PROC_CAN1_RX: U1.B3, U5.4
PROC_CAN1_TX: U1.A3, U5.1
PROC_LPUART1_CTS: U1.G4, U3.13
PROC_LPUART1_RTS: U1.G5, U3.15
PROC_LPUART1_RX: U1.E3, U3.16
PROC_LPUART1_TX: U1.E2, U3.14
PROC_SYS_JTCK_SWCLK: R9.1, U1.A7, U2.4
PROC_SYS_JTDI: R7.1, U1.A6, U2.8
PROC_SYS_JTDO_SWO: U1.A5, U2.6
PROC_SYS_JTMS_SWDIO: R8.1, U1.A8, U2.2
RST_OUT_U2_JTAG_RST_B: R6.1, U2.10, U14.1
VCC_S1_15V2: C22.1, C23.1, C26.1, C29.1, C30.1, J1.1, U9.5, U9.8, U10.8
VCC_TIER1_3V3: C1.1, C2.1, C3.1, C4.1, C5.1, C6.1, C7.1, C8.1, C9.1, C10.1, C13.1, C17.1, C18.1, C20.1, C21.1, C24.1, C25.1, C28.1, C31.1, C32.1, I1.1, R4.2, R6.2, R7.2, R8.2, R11.2, R13.1, R18.2, R19.2, R21.1, U1.B2, U1.D2, U1.E4, U1.E5, U1.E6, U1.H1, U2.1, U3.5, U3.12, U5.5, U8.4, U9.1, U11.6, U14.5, U15.5
VCC_TIER1_5V0: C19.1, C27.1, R15.2, R16.1, U5.3, U10.1
